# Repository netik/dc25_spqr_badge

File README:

In this folder you will find the KiCad board, schematic, and 
fabrication outputs for our Unofficial DEFCON 25 badge.

Stuff in the fabrication folder was set to MacroFab for prototype v1
on 12/20/2016. At today's prices, a board costs about $216 to make, or
$500 for two. This is for a 4-sided board and is not recommended.

Fabrication-rev4 contains our final and hopefully production gerbers.

Cost is approximately $180 / board for a single run, and this cost 
goes down as you make more boards.

The firmware is available in the cibios-orchard repo.
We are very close to release and this code is nearly in it's final 
form.
--
@netik
05/04/2017

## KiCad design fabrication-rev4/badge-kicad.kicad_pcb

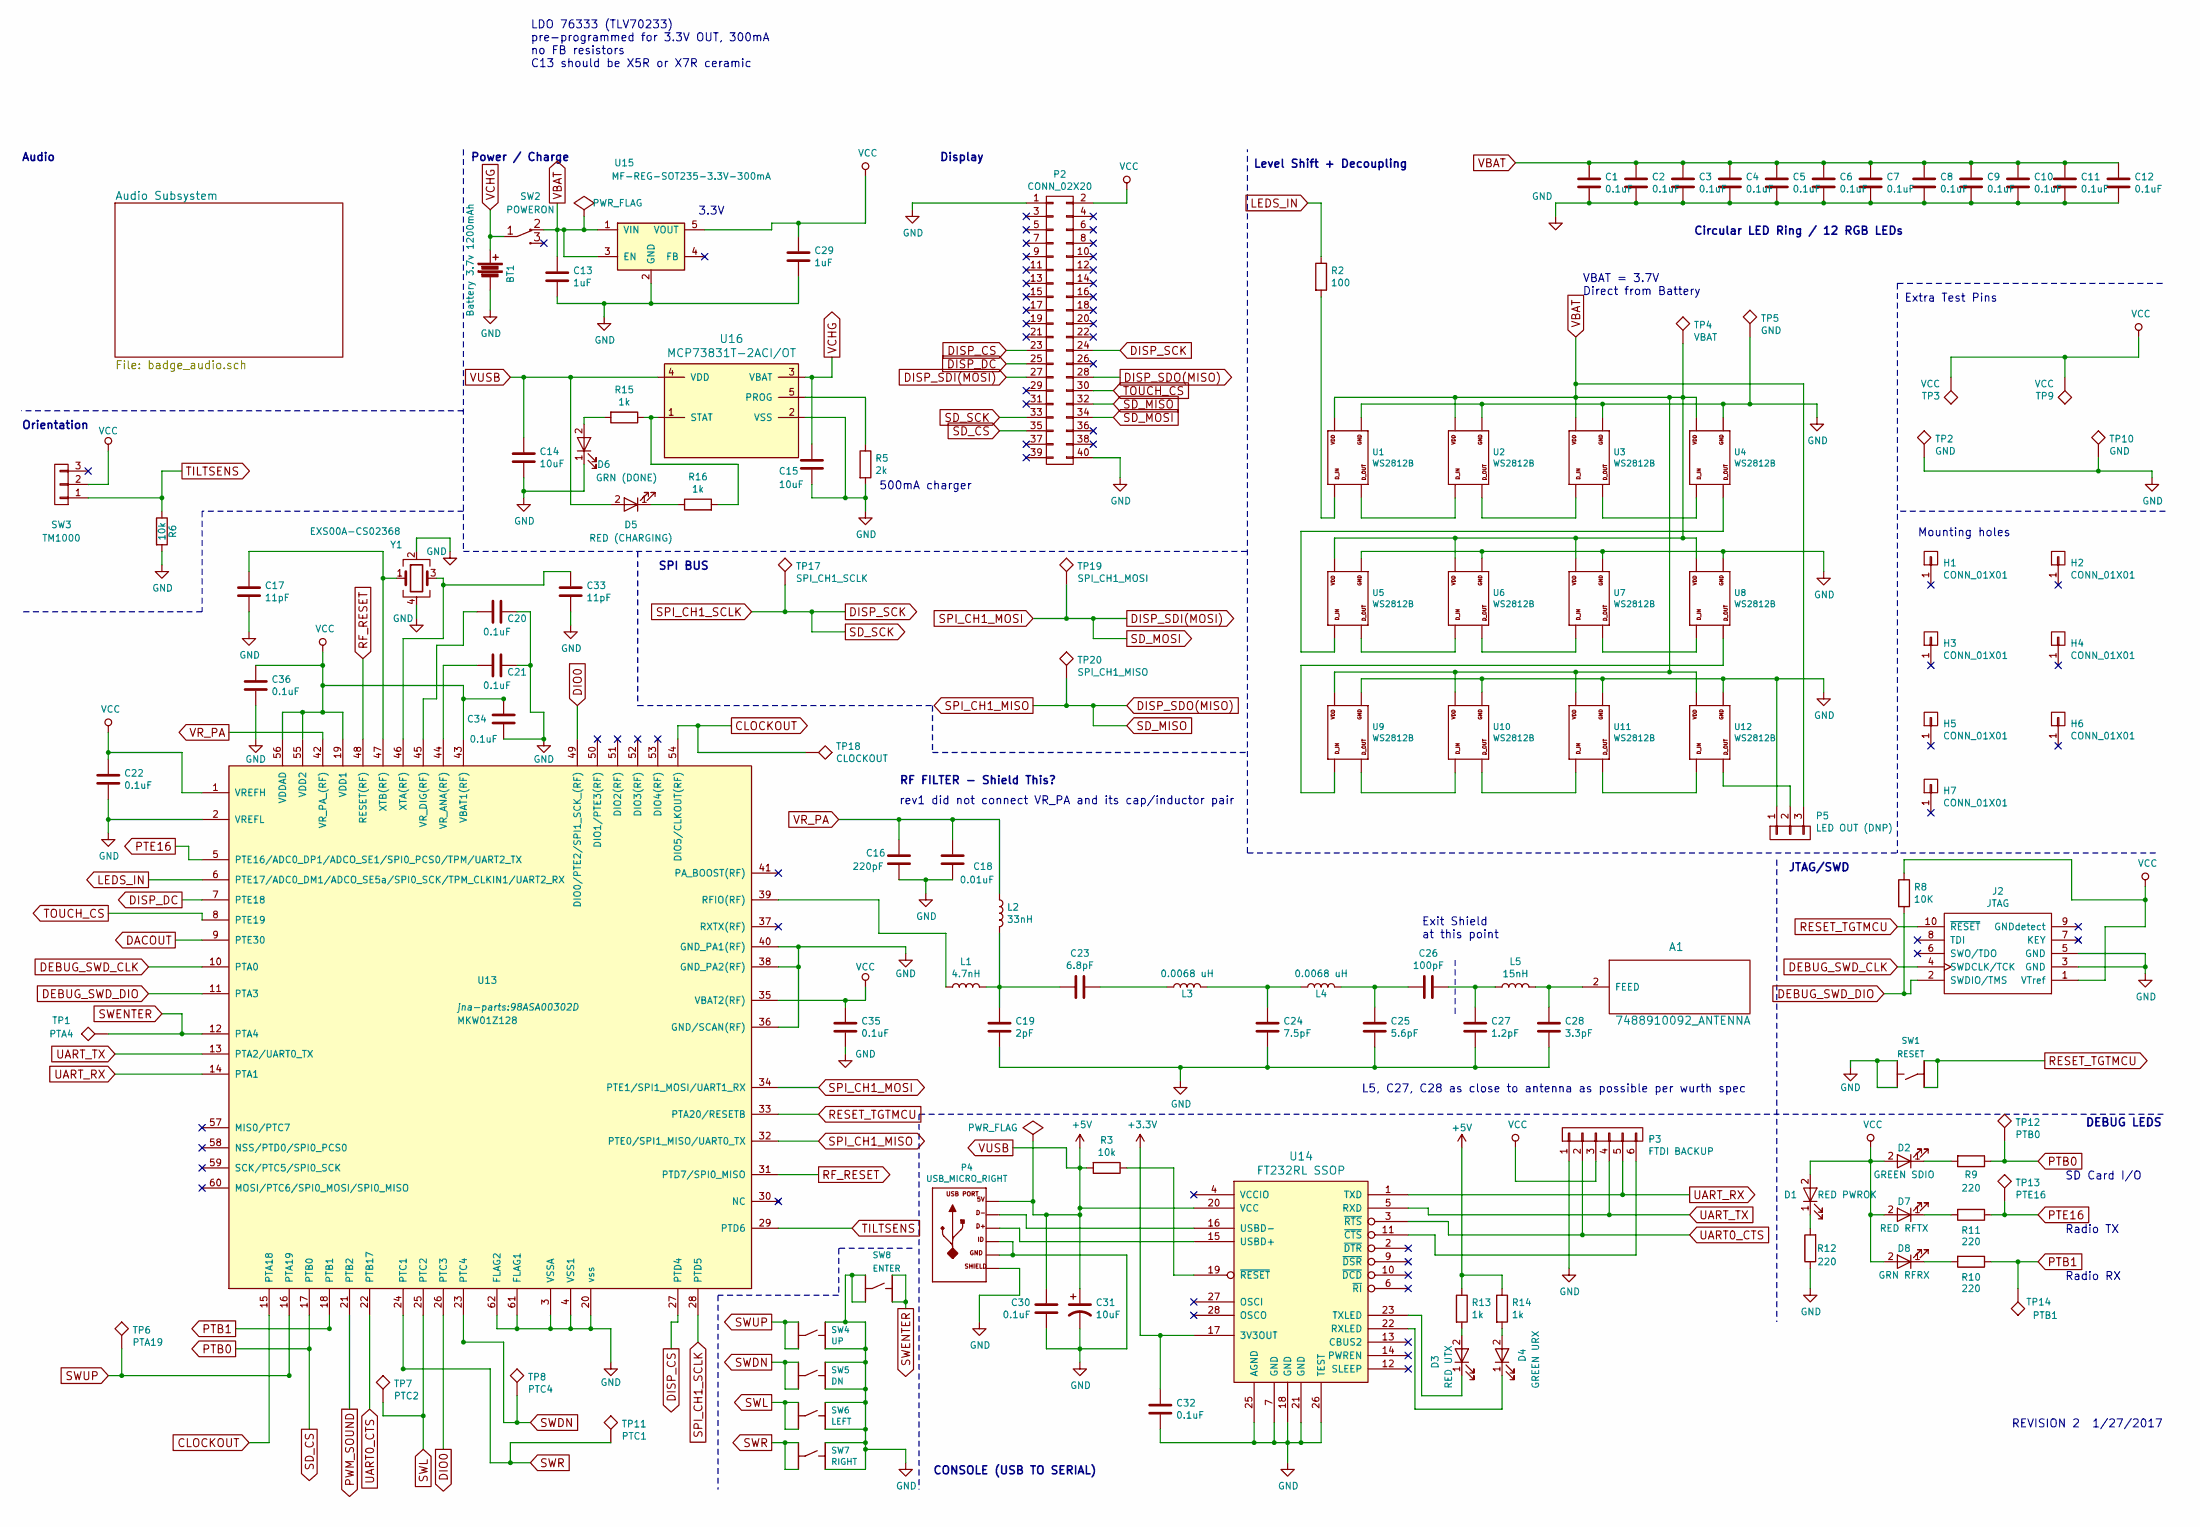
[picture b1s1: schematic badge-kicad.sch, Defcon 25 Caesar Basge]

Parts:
A1: 7488910092_ANTENNA; Antenna_Wurth_7488910092
BT1: Battery 3.7v 1200mAh; JST_PH_S2B-PH-SM4-TB_02x2.00mm_Angled
C1, C2, C3, C4, C5, C6, C7, C8, C9, C10, C11, C12, C20, C21, C22, C30, C32, C34, C35, C36: 0.1uF; C_0805_HandSoldering
C13, C29: 1uF; C_0805_HandSoldering
C14, C15: 10uF; C_1206
C16: 220pF; C_0805_HandSoldering
C17, C33: 11pF; C_0805_HandSoldering
C18: 0.01uF; C_0603_HandSoldering
C19: 2pF; C_0603_HandSoldering
C23: 6.8pF; C_0603_HandSoldering
C24: 7.5pF; C_0603_HandSoldering
C25: 5.6pF; C_0805_HandSoldering
C26: 100pF; C_0805_HandSoldering
C27: 1.2pF; C_0805_HandSoldering
C28: 3.3pF; C_0805_HandSoldering
C31: 10uF; C_0805_HandSoldering
D1: RED PWROK; LED_0805
D2: GREEN SDIO; LED_0805
D3: RED UTX; LED_0805
D4: GREEN URX; LED_0805
D5: RED (CHARGING); LED_0805
D6: GRN (DONE); LED_0805
D7: RED RFTX; LED_0805
D8: GRN RFRX; LED_0805
H1, H2, H3, H4, H5, H6, H7: CONN_01X01; MountingHole_3.2mm_M3_DIN965
J2: JTAG; Pin_Header_Straight_2x05_Pitch1.27mm
L1: 4.7nH; Neosid_Inductor_SM0603CG
L2: 33nH; Neosid_Inductor_SM0603CG
L3, L4: 0.0068 uH; Neosid_Inductor_SM0603CG
L5: 15nH; Neosid_Inductor_SM0603CG
P2: CONN_02X20; IDC_HEADER_FEMALE
P3: FTDI BACKUP; Pin_Header_Straight_1x06
P4: USB_MICRO_RIGHT; MF_Connectors-MICROUSB-RIGHT
P5: LED OUT (DNP); Pin_Header_Straight_1x03
R2: 100; R_0805
R3, R6: 10k; R_0805
R5: 2k; R_0805
R8: 10K; R_0805
R9, R10, R11, R12: 220; R_0805
R13, R14, R15, R16: 1k; R_0805
SW1: RESET; MF_Switches-TACT4.2MM
SW2: POWERON; SW_SPDT_PCM12
SW3: TM1000
SW4: UP; MF_Switches-TACT4.2MM
SW5: DN; MF_Switches-TACT4.2MM
SW6: LEFT; MF_Switches-TACT4.2MM
SW7: RIGHT; MF_Switches-TACT4.2MM
SW8: ENTER; MF_Switches-TACT4.2MM
TP1: PTA4; Measurement_Point_Round-TH_Small
TP2, TP5, TP10: GND; Measurement_Point_Round-TH_Small
TP3, TP9: VCC; Measurement_Point_Round-TH_Small
TP4: VBAT; Measurement_Point_Round-TH_Small
TP6: PTA19; Measurement_Point_Round-TH_Small
TP7: PTC2; Measurement_Point_Round-TH_Small
TP8: PTC4; Measurement_Point_Round-TH_Small
TP11: PTC1; Measurement_Point_Round-TH_Small
TP12: PTB0; Measurement_Point_Round-TH_Small
TP13: PTE16; Measurement_Point_Round-TH_Small
TP14: PTB1; Measurement_Point_Round-TH_Small
TP17: SPI_CH1_SCLK; Measurement_Point_Round-TH_Small
TP18: CLOCKOUT; Measurement_Point_Round-TH_Small
TP19: SPI_CH1_MOSI; Measurement_Point_Round-TH_Small
TP20: SPI_CH1_MISO; Measurement_Point_Round-TH_Small
U1, U2, U3, U4, U5, U6, U7, U8, U9, U10, U11, U12: WS2812B; MF_LEDs-WS2812B
U13: MKW01Z128; 98ASA00302D
U14: FT232RL SSOP; SSOP-28_5.3x10.2mm_Pitch0.65mm
U15: MF-REG-SOT235-3.3V-300mA; SOT-23-5
U16: MCP73831T-2ACI/OT; SOT-23-5
Y1: EXS00A-CS02368; Crystal_EXS00A-CS02368

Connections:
+3V3: C32.1, U14.17 (3V3OUT)
CLOCKOUT: TP18.1, U13.15 (PTA18), U13.54 (DIO5/CLKOUT(RF))
DACOUT: U13.9 (PTE30); also elsewhere on the board
DEBUG_SWD_CLK: J2.4 (SWDCLK/TCK), U13.10 (PTA0)
DEBUG_SWD_DIO: J2.2 (SWDIO/TMS), R8.2, U13.11 (PTA3)
DIO0: U13.26 (PTC3), U13.49 (DIO0/PTE2/SPI1_SCK_(RF))
DISP_CS: P2.23, U13.27 (PTD4)
DISP_DC: P2.25, U13.7 (PTE18)
DISP_SCK: P2.24, P2.33, TP17.1, U13.28 (PTD5)
DISP_SDI(MOSI): P2.27, P2.34, TP19.1, U13.34 (PTE1/SPI1_MOSI/UART1_RX)
DISP_SDO(MISO): P2.28, P2.32, TP20.1, U13.32 (PTE0/SPI1_MISO/UART0_TX)
GND: BT1.2, C1.2, C2.2, C3.2, C4.2, C5.2, C6.2, C7.2, C8.2, C9.2, C10.2, C11.2, C12.2, C13.2, C14.2, C15.2, C16.2, C17.2, C18.2, C19.2, C20.1, C21.1, C22.2, C24.2, C25.2, C27.2, C28.2, C29.2, C30.2, C31.2, C32.2, C33.2, C34.1, C35.2, C36.2, D6.1 (K), J2.3 (GND), J2.5 (GND), P2.1, P2.40, P3.1, P4.4 (ID), P4.5 (GND), P4.S1 (SLD), P4.S2 (SLD), P4.S3 (SLD), P4.S4 (SLD), P4.S5 (SLD), P4.S6 (SLD), P5.1, R5.2, R6.2, R12.1, SW1.P$1, SW1.P$2, SW4.P$1, SW4.P$2, SW5.P$1, SW5.P$2, SW6.P$1, SW6.P$2, SW7.P$1, SW7.P$2, SW8.P$3, SW8.P$4, TP2.1, TP5.1, TP10.1, U1.P$3 (VSS), U2.P$3 (VSS), U3.P$3 (VSS), U4.P$3 (VSS), U5.P$3 (VSS), U6.P$3 (VSS), U7.P$3 (VSS), U8.P$3 (VSS), U9.P$3 (VSS), U10.P$3 (VSS), U11.P$3 (VSS), U12.P$3 (VSS), U13.2 (VREFL), U13.3 (VSSA), U13.4 (VSS1), U13.20 (vss), U13.36 (GND/SCAN(RF)), U13.38 (GND_PA2(RF)), U13.40 (GND_PA1(RF)), U13.61 (FLAG1), U13.62 (FLAG2), U14.7 (GND), U14.18 (GND), U14.21 (GND), U14.25 (AGND), U14.26 (TEST), U15.2 (GND), U16.2 (VSS), Y1.2, Y1.4; also elsewhere on the board
LEDS_IN: R2.1, U13.6 (PTE17/ADC0_DM1/ADCO_SE5a/SPI0_SCK/TPM_C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)
unnamed: A1.2 (FEED), C28.1, L5.2
unnamed: C17.1, U13.47 (XTB(RF)), Y1.1
unnamed: C19.1, C23.2, L1.2, L2.2
unnamed: C20.2, U13.45 (VR_DIG(RF))
unnamed: C21.2, U13.44 (VR_ANA(RF))
unnamed: C23.1, L3.1
unnamed: C24.1, L3.2, L4.1
unnamed: C25.1, C26.2, L4.2
unnamed: C26.1, C27.1, L5.1
unnamed: C33.1, U13.46 (XTA(RF)), Y1.3
unnamed: D1.1 (K), R12.2
unnamed: D2.1 (K), R9.2
unnamed: D3.1 (K), U14.23 (TXLED)
unnamed: D3.2 (A), R13.2
unnamed: D4.1 (K), U14.22 (RXLED)
unnamed: D4.2 (A), R14.2
unnamed: D5.1 (K), R16.1
unnamed: D6.2 (A), R15.2
unnamed: D7.1 (K), R11.2
unnamed: D8.1 (K), R10.2
unnamed: L1.1, U13.39 (RFIO(RF))
unnamed: P3.6, U14.11 (~CTS)
unnamed: P4.2 (D-), U14.16 (USBD-)
unnamed: P4.3 (D+), U14.15 (USBD+)
unnamed: P5.2, U12.P$2 (DOUT)
unnamed: R2.2, U1.P$4 (DIN)
unnamed: R3.1, U14.19 (~RESET)
unnamed: R5.1, U16.5 (PROG)
unnamed: R15.1, R16.2, U16.1 (STAT)
unnamed: U1.P$2 (DOUT), U2.P$4 (DIN)
unnamed: U2.P$2 (DOUT), U3.P$4 (DIN)
unnamed: U3.P$2 (DOUT), U4.P$4 (DIN)
unnamed: U4.P$2 (DOUT), U5.P$4 (DIN)
unnamed: U5.P$2 (DOUT), U6.P$4 (DIN)
unnamed: U6.P$2 (DOUT), U7.P$4 (DIN)
unnamed: U7.P$2 (DOUT), U8.P$4 (DIN)
unnamed: U8.P$2 (DOUT), U9.P$4 (DIN)
unnamed: U10.P$2 (DOUT), U11.P$4 (DIN)
unnamed: U9.P$2 (DOUT), U10.P$4 (DIN)
unnamed: U11.P$2 (DOUT), U12.P$4 (DIN)
PTB0: P2.35, R9.1, TP12.1, U13.17 (PTB0)
PTB1: R10.1, TP14.1, U13.18 (PTB1)
PTE16: R11.1, TP13.1, U13.5 (PTE16/ADC0_DP1/ADCO_SE1/SPI0_PCS0/TPM/U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)
PWM_SOUND: U13.21 (PTB2); also elsewhere on the board
RESET_TGTMCU: J2.10 (~RESET), SW1.P$3, SW1.P$4, U13.33 (PTA20/RESETB)
RF_RESET: U13.31 (PTD7/SPI0_MISO), U13.48 (RESET(RF))
SWDN: SW5.P$3, SW5.P$4, TP8.1, U13.23 (PTC4)
SWENTER: SW8.P$1, SW8.P$2, TP1.1, U13.12 (PTA4)
SWL: SW6.P$3, SW6.P$4, TP7.1, U13.25 (PTC2)
SWR: SW7.P$3, SW7.P$4, TP11.1, U13.24 (PTC1)
SWUP: SW4.P$3, SW4.P$4, TP6.1, U13.16 (PTA19)
TILTSENS: R6.1, SW3.1, U13.29 (PTD6)
TOUCH_CS: P2.30, U13.8 (PTE19)
UART0_CTS: P3.2, U13.22 (PTB17), U14.3 (~RTS)
UART_RX: P3.5, U13.14 (PTA1), U14.1 (TXD)
UART_TX: P3.4, U13.13 (PTA2/UART0_TX), U14.5 (RXD)
VBAT: C1.1, C2.1, C3.1, C4.1, C5.1, C6.1, C7.1, C8.1, C9.1, C10.1, C11.1, C12.1, C13.1, P5.3, SW2.2 (NC), TP4.1, U1.P$1 (VDD), U2.P$1 (VDD), U3.P$1 (VDD), U4.P$1 (VDD), U5.P$1 (VDD), U6.P$1 (VDD), U7.P$1 (VDD), U8.P$1 (VDD), U9.P$1 (VDD), U10.P$1 (VDD), U11.P$1 (VDD), U12.P$1 (VDD), U15.1 (VIN), U15.3 (EN); also elsewhere on the board
VCC: C22.1, C29.1, C34.2, C35.1, C36.1, D1.2 (A), D2.2 (A), D7.2 (A), D8.2 (A), J2.1 (VTref), P2.2, P3.3, R8.1, SW3.2, TP3.1, TP9.1, U13.1 (VREFH), U13.19 (VDD1), U13.35 (VBAT2(RF)), U13.43 (VBAT1(RF)), U13.55 (VDD2), U13.56 (VDDAD), U15.5 (VOUT)
VCHG: BT1.1, C15.1, SW2.1 (COM), U16.3 (VBAT)
VR_PA: C16.1, C18.1, L2.1, U13.42 (VR_PA_(RF))
VUSB: C14.1, C30.1, C31.1, D5.2 (A), P4.1 (5V), R3.2, R13.1, R14.1, U14.20 (VCC), U16.4 (VDD)

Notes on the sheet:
Level Shift + Decoupling
Circular LED Ring / 12 RGB LEDs
JTAG/SWD
Display
Audio
Power / Charge
RF FILTER - Shield This?
SPI BUS
Orientation
CONSOLE (USB TO SERIAL)
DEBUG LEDS
LDO 76333 (TLV70233) pre-programmed for 3.3V OUT, 300mA no FB resistors C13 should be X5R or X7R ceramic
500mA charger
3.3V
VBAT = 3.7V Direct from Battery
Radio RX
Radio TX
SD Card I/O
rev1 did not connect VR_PA and its cap/inductor pair
L5, C27, C28 as close to antenna as possible per wurth spec
Exit Shield at this point
Mounting holes
Extra Test Pins
REVISION 2 1/27/2017

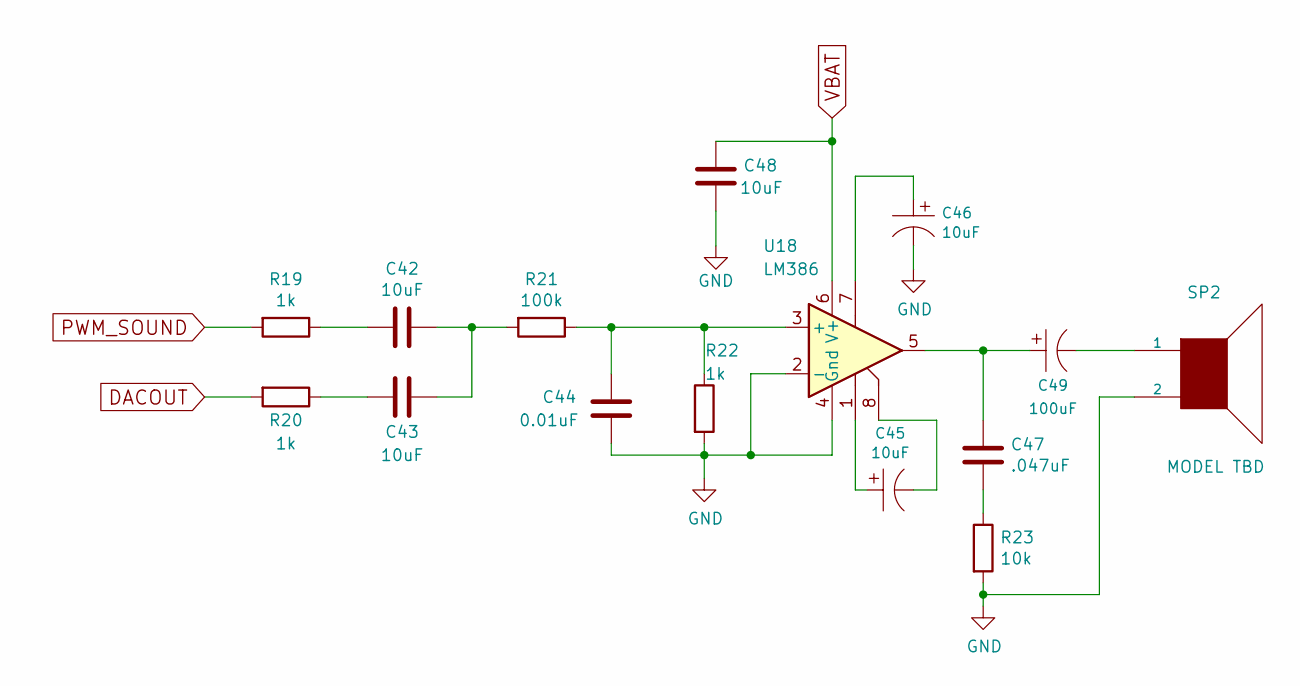
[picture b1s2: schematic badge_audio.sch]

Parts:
C42, C43, C48: 10uF; C_0805_HandSoldering
C44: 0.01uF; C_0603_HandSoldering
C45, C46: 10uF; MF_Passives-CP4MM
C47: .047uF; C_0805_HandSoldering
C49: 100uF; MF_Passives-CP6.3MM
R19, R20, R22: 1k; R_0805
R21: 100k; R_0805
R23: 10k; R_0805
SP2: MODEL TBD; SPEAKER_AST_01708MR_R
U18: LM386; SOIC-8-N

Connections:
DACOUT: R20.2; also elsewhere on the board
GND: C44.2, C46.P$2, C48.2, R22.2, R23.2, SP2.2, U18.2 (-), U18.4 (Gnd); also elsewhere on the board
unnamed: C42.1, C43.1, R21.2
unnamed: C42.2, R19.1
unnamed: C43.2, R20.1
unnamed: C44.1, R21.1, R22.1, U18.3 (+)
unnamed: C45.P$1, U18.1
unnamed: C45.P$2, U18.8
unnamed: C46.P$1, U18.7
unnamed: C47.1, C49.P$1, U18.5
unnamed: C47.2, R23.1
unnamed: C49.P$2, SP2.1
PWM_SOUND: R19.2; also elsewhere on the board
VBAT: C48.1, U18.6 (V+); also elsewhere on the board

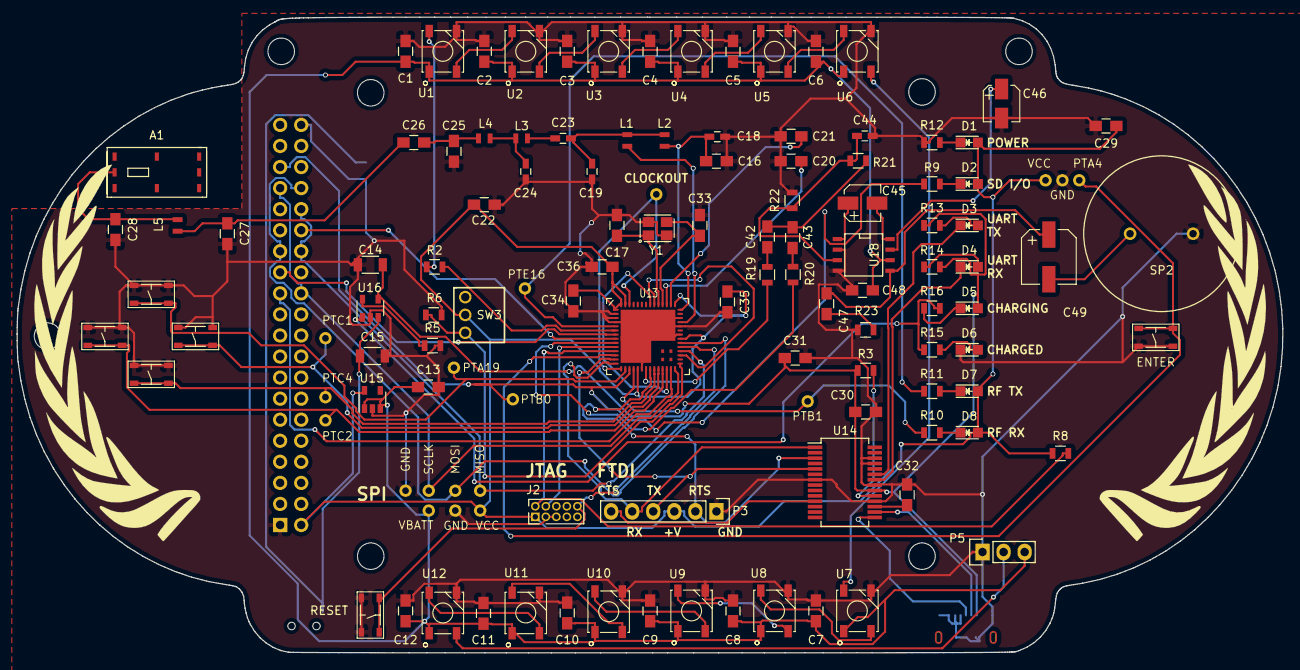
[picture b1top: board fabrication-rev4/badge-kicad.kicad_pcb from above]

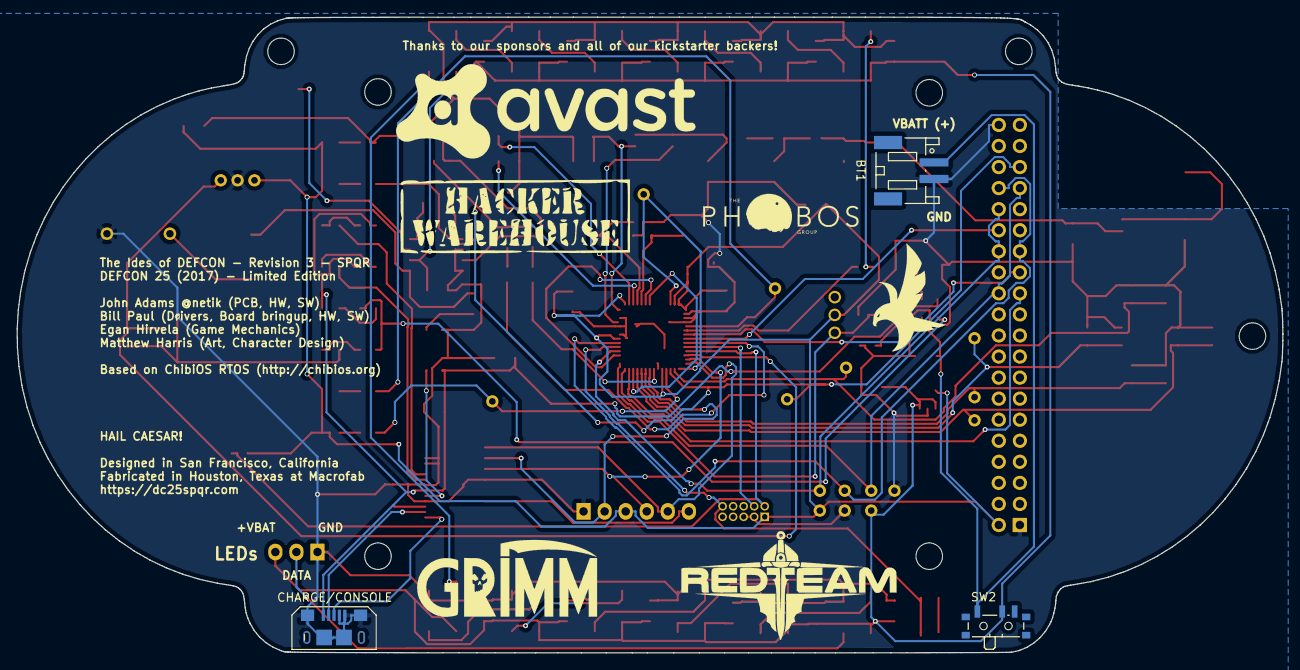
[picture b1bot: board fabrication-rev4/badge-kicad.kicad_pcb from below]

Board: 2 copper layers, 152.7 x 76.7 mm, 134 parts (3 on the bottom side), 84 nets.

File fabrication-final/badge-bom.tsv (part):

# Generated by MacroFab for PCB 4dj0a6, version 10.
# DESIGNATOR	X_LOC	Y_LOC	ROTATION	SIDE	TYPE	X_SIZE	Y_SIZE	VALUE	FOOTPRINT	POPULATE	MPN	MPN1	MPN2	MPN3
""	2381.84	2081.92	180	2	2	0	0	"	logos:phobos_19mm_x_5.5mm	0					
""	2381.84	2081.92	180	2	2	0	0	"	logos:hw_200dpi	0					
""	2381.84	2081.92	180	2	2	0	0	"	logos:grimm_600dpi	0					
""	2381.84	2081.92	180	2	2	0	0	"	logos:redteam_31_40	0					
""	2381.84	2081.92	180	2	2	0	0	"	logos:laurel_right	0					
""	2381.84	2081.92	180	2	2	0	0	"	logos:laurel	0					
A1	663.338	2281.92	180	1	1	421.26	188.976	7488910092_ANTENNA	jna-parts:Antenna_Wurth_7488910092	1	7488910092				7488910092
BT1	1764.72	2289.79	270	2	1	330.709	354.331	Battery 3.7v 1000mAh	Connectors_JST:JST_PH_S2B-PH-SM4-TB_02x2.00mm_Angled	1	1769				1769
C1	1844.44	2856.72	90	1	1	157.48	49.2126	0.1uF	Capacitors_SMD:C_0805_HandSoldering	1					
C10	2612.16	189.4	90	1	1	157.48	49.2126	0.1uF	Capacitors_SMD:C_0805_HandSoldering	1					
C11	2214.52	187.431	90	1	1	157.48	49.2126	0.1uF	Capacitors_SMD:C_0805_HandSoldering	1					
C12	1844.44	199.242	90	1	1	157.48	49.2126	0.1uF	Capacitors_SMD:C_0805_HandSoldering	1					
C13	1952.71	1262.23	0	1	1	157.48	49.2126	1uF	Capacitors_SMD:C_0805_HandSoldering	1					
C14	1677.12	1842.94	180	1	1	157.48	62.9921	10uF	Capacitors_SMD:C_1206	1					
C15	1686.96	1409.87	0	1	1	157.48	62.9921	10uF	Capacitors_SMD:C_1206	1					
C16	3320.82	2335.07	0	1	1	157.48	49.2126	220pF	Capacitors_SMD:C_0805_HandSoldering	1	C0805C221K5GACTU				C0805C221K5GACTU
C17	2848.38	2029.95	90	1	1	157.48	49.2126	11pF	Capacitors_SMD:C_0805_HandSoldering	1	C0805C110J5GACTU				C0805C110J5GACTU
C18	3324.75	2451.21	0	1	1	122.047	29.5276	0.01uF	Capacitors_SMD_C_0603_HandSoldering	1	MF-CAP-0603-0.01uF				MF-CAP-0603-0.01uF
C19	2730.27	2285.86	270	1	1	122.047	29.5276	2pF	Capacitors_SMD:C_0603_HandSoldering	1	C1608C0G1H020C080AA				C1608C0G1H020C080AA
C2	2218.46	2856.72	90	1	1	157.48	49.2126	0.1uF	Capacitors_SMD:C_0805_HandSoldering	1					
C20	3675.15	2335.07	0	1	1	157.48	49.2126	0.1uF	Capacitors_SMD:C_0805_HandSoldering	1					
C21	3675.15	2453.18	0	1	1	157.48	49.2126	0.1uF	Capacitors_SMD:C_0805_HandSoldering	1					
C22	2218.46	2128.38	0	1	1	157.48	49.2126	0.1uF	Capacitors_SMD:C_0805_HandSoldering	1					
C23	2592.47	2443.34	0	1	1	122.047	29.5276	6.8pF	Capacitors_SMD_C_0603_HandSoldering	1	06035A6R8CAT2A				06035A6R8CAT2A
C24	2415.31	2285.86	270	1	1	122.047	29.5276	7.5pF	0603	1	251R14S7R5CV4T				251R14S7R5CV4T
C25	2074.36	2381.92	270	1	1	157.48	49.2126	5.6pF	Capacitors_SMD:C_0805_HandSoldering	1	CL21C5R6CBANNNC				CL21C5R6CBANNNC
C26	1883.81	2423.65	0	1	1	157.48	49.2126	100pF	Capacitors_SMD:C_0805_HandSoldering	1	08055A101KAT2A				08055A101KAT2A
C27	997.983	1990.58	270	1	1	157.48	49.2126	1.2pF	Capacitors_SMD:C_0805_HandSoldering	1	CL21C1R2BBANNNC				CL21C1R2BBANNNC
C28	466.487	2010.27	270	1	1	157.48	49.2126	3.3pF	Capacitors_SMD:C_0805_HandSoldering	1	08055A3R3CAT2A				08055A3R3CAT2A
C29	5171.21	2502.39	180	1	1	157.48	49.2126	1uF	Capacitors_SMD:C_0805_HandSoldering	1					
C3	2612.16	2856.72	90	1	1	157.48	49.2126	0.1uF	Capacitors_SMD:C_0805_HandSoldering	1					
C30	4029.48	1144.12	0	1	1	157.48	49.2126	0.1uF	Capacitors_SMD:C_0805_HandSoldering	1					
C31	3694.83	1400.03	0	1	1	157.48	49.2126	10uF	Capacitors_SMD:C_0805_HandSoldering	1	CL21A106KQCLRNC				CL21A106KQCLRNC
C32	4226.33	750.423	90	1	1	157.48	49.2126	0.1uF	Capacitors_SMD:C_0805_HandSoldering	1					
C33	3242.08	2029.95	90	1	1	157.48	49.2126	11pF	Capacitors_SMD:C_0805_HandSoldering	1	C0805C110J5GACTU				C0805C110J5GACTU
C34	2641.29	1671.29	90	1	1	157.48	49.2126	0.1uF	Capacitors_SMD:C_0805_HandSoldering	1					
C35	3372.98	1666.76	270	1	1	157.48	49.2126	0.1uF	Capacitors_SMD:C_0805_HandSoldering	1					
C36	2777.9	1833.1	180	1	1	157.48	49.2126	0.1uF	Capacitors_SMD:C_0805_HandSoldering	1					
C4	3005.86	2856.72	90	1	1	157.48	49.2126	0.1uF	Capacitors_SMD:C_0805_HandSoldering	1					
C42	3562.55	1975.23	270	1	1	157.48	49.2126	10uF	Capacitors_SMD:C_0805_HandSoldering	1	CL21A106KQCLRNC				CL21A106KQCLRNC
C43	3682.63	1971.68	270	1	1	157.48	49.2126	Capacitors_SMD:C_0805_HandSoldering	1	1	CL21A106KQCLRNC			CL21A106KQCLRNC	CL21A106KQCLRNC
C44	4025.54	2455.15	0	1	1	122.047	29.5276	0.01uF	Capacitors_SMD_C_0603_HandSoldering	1	MF-CAP-0603-0.01uF				MF-CAP-0603-0.01uF
C45	4014.52	2135.86	270	1	1	98.4	200.5	10uF	MF_Passives:MF_Passives-CP4MM	1	MF-CAP-4MM-10uF				MF-CAP-4MM-10uF
C46	4675.15	2608.69	180	1	1	98.4	200.5	10uF	MF_Passives:MF_Passives-CP4MM	1	MF-CAP-4MM-10uF				MF-CAP-4MM-10uF
C47	3844.05	1657.9	270	1	1	157.48	49.2126	.047uF	Capacitors_SMD:C_0805_HandSoldering	1	08053C473JAT2A				08053C473JAT2A
C48	4014.52	1721.68	180	1	1	157.48	49.2126	10uF	Capacitors_SMD:C_0805_HandSoldering	1	CL21A106KQCLRNC				CL21A106KQCLRNC
C49	4899.56	1880.34	180	1	1	125.9	275.3	100uF	MF_Passives:MF_Passives-CP6.3MM	1	MF-CAP-6.3MM-100uF				MF-CAP-6.3MM-100uF
C5	3399.56	2856.72	90	1	1	157.48	49.2126	0.1uF	Capacitors_SMD:C_0805_HandSoldering	1					
C6	3793.26	2856.72	90	1	1	157.48	49.2126	0.1uF	Capacitors_SMD:C_0805_HandSoldering	1					
C7	3793.26	199.242	90	1	1	157.48	49.2126	0.1uF	Capacitors_SMD:C_0805_HandSoldering	1					
C8	3399.56	199.242	90	1	1	157.48	49.2126	0.1uF	Capacitors_SMD:C_0805_HandSoldering	1					
C9	3005.86	199.242	90	1	1	157.48	49.2126	0.1uF	Capacitors_SMD:C_0805_HandSoldering	1					
D1	4521.61	2423.65	0	1	1	129.8	47.2	RED PWROK	LEDs:LED_0805	1	MF-LED-0805-RED				MF-LED-0805-RED
D2	4521.61	2226.8	0	1	1	129.8	47.2	GREEN SDIO	LEDs:LED_0805	1	MF-LED-0805-GREEN				MF-LED-0805-GREEN
D3	4521.61	2029.95	0	1	1	129.8	47.2	RED UTX	LEDs:LED_0805	1	MF-LED-0805-RED				MF-LED-0805-RED
D4	4521.61	1833.1	0	1	1	129.8	47.2	GREEN URX	LEDs:LED_0805	1	MF-LED-0805-GREEN				MF-LED-0805-GREEN
D5	4521.61	1636.25	0	1	1	129.8	47.2	RED (CHARGING)	LEDs:LED_0805	1	MF-LED-0805-RED				MF-LED-0805-RED
D6	4521.61	1439.4	0	1	1	129.8	47.2	GRN (DONE)	LEDs:LED_0805	1	MF-LED-0805-GREEN				MF-LED-0805-GREEN
D7	4521.61	1242.55	0	1	1	129.8	47.2	RED RFTX	LEDs:LED_0805	1	MF-LED-0805-RED				MF-LED-0805-RED
D8	4521.61	1045.7	0	1	1	129.8	47.2	GRN RFRX	LEDs:LED_0805	1	MF-LED-0805-GREEN				MF-LED-0805-GREEN
H1	1679.09	2659.87	0	1	2	125.984	125.984	CONN_01X01	Mounting_Holes_MountingHole_3_2mm_M3_DIN965	0					
H2	4297.2	2663.81	0	1	2	125.984	125.984	CONN_01X01	Mounting_Holes_MountingHole_3_2mm_M3_DIN965	0					
H3	1679.09	459.085	0	1	2	125.984	125.984	CONN_01X01	Mounting_Holes_MountingHole_3_2mm_M3_DIN965	0					
H4	4297.2	459.085	0	1	2	125.984	125.984	CONN_01X01	Mounting_Holes_MountingHole_3_2mm_M3_DIN965	0					
H5	1253.89	2856.72	0	1	2	125.984	125.984	CONN_01X01	Mounting_Holes_MountingHole_3_2mm_M3_DIN965	0					
H6	4757.83	2856.72	0	1	2	125.984	125.984	CONN_01X01	Mounting_Holes_MountingHole_3_2mm_M3_DIN965	0					
H7	144.046	1504.2	0	1	2	125.984	125.984	CONN_01X01	Mounting_Holes_MountingHole_3_2mm_M3_DIN965	0					
J2	2560.58	671.093	90	1	2	91.3386	241.339	JTAG	Pin_Headers:Pin_Header_Straight_2x05_Pitch1.27mm	1	M50-3500542				M50-3500542
L1	2897.59	2433.49	90	1	1	78.8	47.2	4.7nH	Inductors_NEOSID:Neosid_Inductor_SM0603CG	1	LQG18HN4N7S00D				LQG18HN4N7S00D
L2	3074.75	2433.49	90	1	1	78.8	47.2	33nH	Inductors_NEOSID:Neosid_Inductor_SM0603CG	1	CI160808-33NJ				CI160808-33NJ
L3	2395.62	2443.34	180	1	1	78.8	47.2	0.0068 uH	Inductors_NEOSID:Neosid_Inductor_SM0603CG	1	CI160808-6N8J				CI160808-6N8J
L4	2218.46	2443.34	180	1	1	78.8	47.2	0.0068 uH	Inductors_NEOSID:Neosid_Inductor_SM0603CG	1	CI160808-6N8J				CI160808-6N8J
L5	761.763	2029.95	90	1	1	78.8	47.2	15nH	Inductors_NEOSID_Neosid_Inductor_SM0603CG	1	HK160815NJ-T				HK160815NJ-T
P2	1298.77	1557.19	90	1	2	1968	168	CONN_02X20	jna-parts:IDC_HEADER_FEMALE	1	SFH11-PBPC-D20-ST-BK				SFH11-PBPC-D20-ST-BK
P3	3070.82	671.683	270	1	2	80	568	FTDI BACKUP	Pin_Headers_Pin_Header_Straight_1x06	0					
P4	4505.86	122.751	180	2	1	306.9	174.15	USB_MICRO_RIGHT	MF_Connectors:MF_Connectors-MICROUSB-RIGHT	1	105017-0001				MF-CON-MICROUSB-RIGHT
P5	4684.6	478.77	90	1	2	80	268	LED OUT (DNP)	Pin_Headers_Pin_Header_Straight_1x03	0					
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
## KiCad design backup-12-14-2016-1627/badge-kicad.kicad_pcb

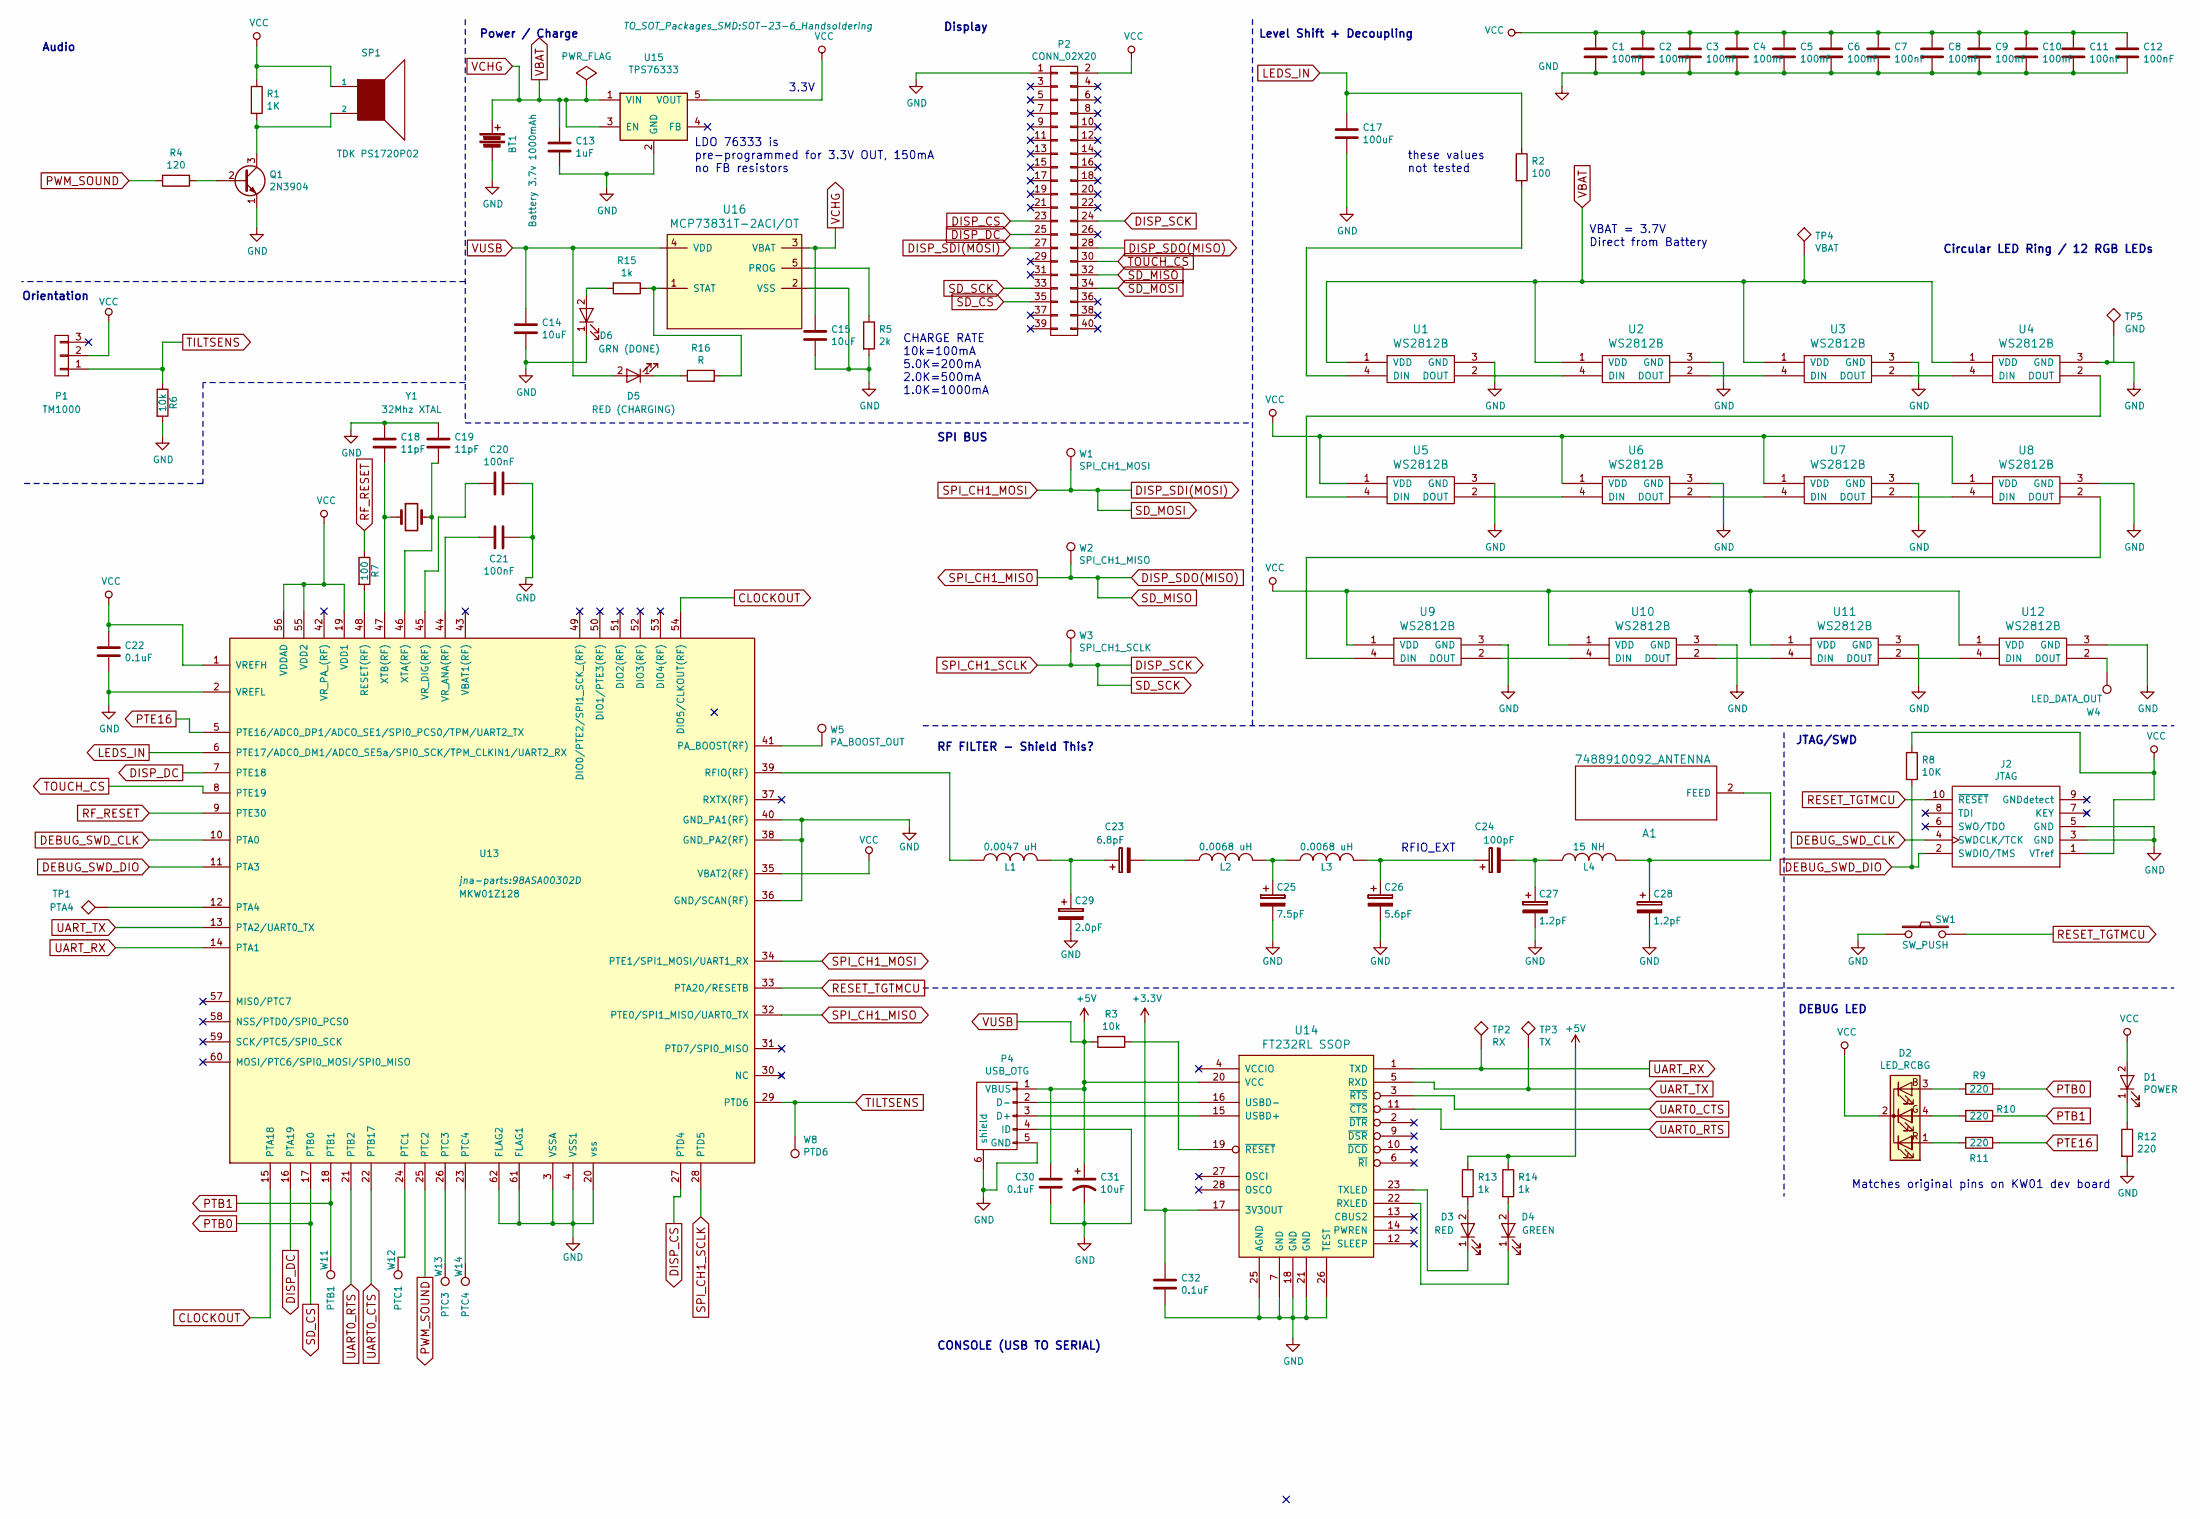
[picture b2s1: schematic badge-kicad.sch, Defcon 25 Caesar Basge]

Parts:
A1: 7488910092_ANTENNA; Antenna_Wurth_7488910092
BT1: Battery 3.7v 1000mAh; JST_PH_S2B-PH-SM4-TB_02x2.00mm_Angled
C1, C2, C3, C4, C5, C6, C7, C8, C9, C10, C11, C12, C20, C21: 100nF; C_1206
C13: 1uF; C_1206
C14, C15, C31: 10uF; C_1206
C17: 100uF; C_1206
C18, C19: 11pF; C_1206
C22, C30, C32: 0.1uF; C_1206
C23: 6.8pF; C_1206
C24: 100pF; C_1206
C25: 7.5pF; C_1206
C26: 5.6pF; C_1206
C27, C28: 1.2pF; C_1206
C29: 2.0pF; C_1206
D1: POWER; LED_1206
D2: LED_RCBG; LED-RGB-5MM_Common_Cathode
D3: RED; LED_1206
D4: GREEN; LED_1206
D5: RED (CHARGING); LED_1206
D6: GRN (DONE); LED_1206
J2: JTAG; IDC_Header_Straight_10pins
L1: 0.0047 uH; Neosid_Inductor_SM1206
L2, L3: 0.0068 uH; Neosid_Inductor_SM1206
L4: 15 NH; Neosid_Inductor_SM1206
P1: TM1000
P2: CONN_02X20; IDC_Header_Straight_40pins
P4: USB_OTG; USB_Mini-B
Q1: 2N3904; SOT-323
R1: 1K; R_1206
R2, R7: 100; R_1206
R3, R6: 10k; R_1206
R4: 120; R_1206
R5: 2k; R_1206
R8: 10K; R_1206
R9, R10, R11, R12: 220; R_1206
R13, R14, R15: 1k; R_1206
R16: R; R_1206
SP1: TDK PS1720P02; TDK_PS1720PD2
SW1: SW_PUSH; SW_SPST_B3S-1000
TP1: PTA4; Test_Point_Keystone_5005-5009_Compact
TP2: RX; Test_Point_Keystone_5005-5009_Compact
TP3: TX; Test_Point_Keystone_5005-5009_Compact
TP4: VBAT; Test_Point_Keystone_5005-5009_Compact
TP5: GND; Test_Point_Keystone_5005-5009_Compact
U1, U2, U3, U4, U5, U6, U7, U8, U9, U10, U11, U12: WS2812B; LED_WS2812B-PLCC4
U13: MKW01Z128; 98ASA00302D
U14: FT232RL SSOP; SSOP-28_5.3x10.2mm_Pitch0.65mm
U15: TPS76333; SOT-23-6_Handsoldering
U16: MCP73831T-2ACI/OT; SOT-23-5
W1: SPI_CH1_MOSI; Test_Point_Keystone_5005-5009_Compact
W2: SPI_CH1_MISO; Test_Point_Keystone_5005-5009_Compact
W3: SPI_CH1_SCLK; Test_Point_Keystone_5005-5009_Compact
W4: LED_DATA_OUT; Test_Point_Keystone_5005-5009_Compact
W5: PA_BOOST_OUT; Test_Point_Keystone_5005-5009_Compact
W8: PTD6; Test_Point_Keystone_5005-5009_Compact
W11: PTB1; Test_Point_Keystone_5005-5009_Compact
W12: PTC1; Test_Point_Keystone_5005-5009_Compact
W13: PTC3; Test_Point_Keystone_5005-5009_Compact
W14: PTC4; Test_Point_Keystone_5005-5009_Compact
Y1: 32Mhz XTAL; Crystal_SMD_0603_4Pads

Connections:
+3V3: C32.1, U14.17 (3V3OUT)
CLOCKOUT: U13.15 (PTA18), U13.54 (DIO5/CLKOUT(RF))
DEBUG_SWD_CLK: J2.4 (SWDCLK/TCK), U13.10 (PTA0)
DEBUG_SWD_DIO: J2.2 (SWDIO/TMS), R8.2, U13.11 (PTA3)
DISP_CS: P2.23, U13.27 (PTD4)
DISP_DC: P2.25, U13.7 (PTE18), U13.16 (PTA19)
DISP_SCK: P2.24, P2.33, U13.28 (PTD5), W3.1
DISP_SDI(MOSI): P2.27, P2.34, U13.34 (PTE1/SPI1_MOSI/UART1_RX), W1.1
DISP_SDO(MISO): P2.28, P2.32, U13.32 (PTE0/SPI1_MISO/UART0_TX), W2.1
GND: BT1.2, C1.2, C2.2, C3.2, C4.2, C5.2, C6.2, C7.2, C8.2, C9.2, C10.2, C11.2, C12.2, C13.2, C14.2, C15.2, C17.2, C18.1, C19.1, C20.1, C21.1, C22.2, C25.2, C26.2, C27.2, C28.2, C29.2, C30.2, C31.2, C32.2, D6.1 (K), J2.3 (GND), J2.5 (GND), P2.1, P4.4 (ID), P4.5 (GND), P4.6 (shield), Q1.1 (E), R5.2, R6.2, R12.2, SW1.1, TP5.1, U1.3 (GND), U2.3 (GND), U3.3 (GND), U4.3 (GND), U5.3 (GND), U6.3 (GND), U7.3 (GND), U8.3 (GND), U9.3 (GND), U10.3 (GND), U11.3 (GND), U12.3 (GND), U13.2 (VREFL), U13.3 (VSSA), U13.4 (VSS1), U13.20 (vss), U13.36 (GND/SCAN(RF)), U13.38 (GND_PA2(RF)), U13.40 (GND_PA1(RF)), U13.61 (FLAG1), U13.62 (FLAG2), U14.7 (GND), U14.18 (GND), U14.21 (GND), U14.25 (AGND), U14.26 (TEST), U15.2 (GND), U16.2 (VSS)
LEDS_IN: C17.1, R2.1, U13.6 (PTE17/ADC0_DM1/ADCO_SE5a/SPI0_SCK/TPM_C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)
unnamed 11: R3.1, U14.19 (~RESET); also elsewhere on the board
unnamed: A1.2 (FEED), C28.1, L4.2
unnamed: C18.2, U13.47 (XTB(RF)), Y1.1
unnamed: C19.2, U13.46 (XTA(RF)), Y1.2
unnamed: C20.2, U13.45 (VR_DIG(RF))
unnamed: C21.2, U13.44 (VR_ANA(RF))
unnamed: C23.1, C29.1, L1.2
unnamed: C23.2, L2.1
unnamed: C24.1, C26.1, L3.2
unnamed: C24.2, C27.1, L4.1
unnamed: C25.1, L2.2, L3.1
unnamed: D1.1 (K), R12.1
unnamed: D2.1 (RA), R11.2
unnamed: D2.3 (BA), R9.2
unnamed: D2.4 (GA), R10.2
unnamed: D3.1 (K), U14.23 (TXLED)
unnamed: D3.2 (A), R13.2
unnamed: D4.1 (K), U14.22 (RXLED)
unnamed: D4.2 (A), R14.2
unnamed: D5.1 (K), R16.1
unnamed: D6.2 (A), R15.2
unnamed: L1.1, U13.39 (RFIO(RF))
unnamed: P4.2 (D-), U14.16 (USBD-)
unnamed: P4.3 (D+), U14.15 (USBD+)
unnamed: Q1.2 (B), R4.1
unnamed: Q1.3 (C), R1.2, SP1.2
unnamed: R2.2, U1.4 (DIN)
unnamed: R5.1, U16.5 (PROG)
unnamed: R7.2, U13.48 (RESET(RF))
unnamed: R15.1, R16.2, U16.1 (STAT)
unnamed: TP1.1, U13.12 (PTA4)
unnamed: U1.2 (DOUT), U2.4 (DIN)
unnamed: U2.2 (DOUT), U3.4 (DIN)
unnamed: U3.2 (DOUT), U4.4 (DIN)
unnamed: U4.2 (DOUT), U5.4 (DIN)
unnamed: U5.2 (DOUT), U6.4 (DIN)
unnamed: U6.2 (DOUT), U7.4 (DIN)
unnamed: U7.2 (DOUT), U8.4 (DIN)
unnamed: U8.2 (DOUT), U9.4 (DIN)
unnamed: U10.2 (DOUT), U11.4 (DIN)
unnamed: U9.2 (DOUT), U10.4 (DIN)
unnamed: U11.2 (DOUT), U12.4 (DIN)
unnamed: U12.2 (DOUT), W4.1
unnamed: U13.23 (PTC4), W14.1
unnamed: U13.24 (PTC1), W12.1
unnamed: U13.26 (PTC3), W13.1
unnamed: U13.41 (PA_BOOST(RF)), W5.1
PTB0: P2.35, R9.1, U13.17 (PTB0)
PTB1: R10.1, U13.18 (PTB1), W11.1
PTE16: R11.1, U13.5 (PTE16/ADC0_DP1/ADCO_SE1/SPI0_PCS0/TPM/U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)
PWM_SOUND: R4.2, U13.25 (PTC2)
RESET_TGTMCU: J2.10 (~RESET), SW1.2, U13.33 (PTA20/RESETB)
RF_RESET: R7.1, U13.9 (PTE30)
TILTSENS: P1.1, R6.1, U13.29 (PTD6), W8.1
TOUCH_CS: P2.30, U13.8 (PTE19)
UART0_CTS: U13.22 (PTB17), U14.3 (~RTS)
UART0_RTS: U13.21 (PTB2), U14.11 (~CTS)
UART_RX: TP2.1, U13.14 (PTA1), U14.1 (TXD)
UART_TX: TP3.1, U13.13 (PTA2/UART0_TX), U14.5 (RXD)
VBAT: BT1.1, C13.1, C15.1, TP4.1, U1.1 (VDD), U2.1 (VDD), U3.1 (VDD), U4.1 (VDD), U15.1 (VIN), U15.3 (EN), U16.3 (VBAT)
VCC: C1.1, C2.1, C3.1, C4.1, C5.1, C6.1, C7.1, C8.1, C9.1, C10.1, C11.1, C12.1, C22.1, D1.2 (A), D2.2 (K), J2.1 (VTref), P1.2, P2.2, R1.1, R8.1, SP1.1, U5.1 (VDD), U6.1 (VDD), U7.1 (VDD), U8.1 (VDD), U9.1 (VDD), U10.1 (VDD), U11.1 (VDD), U12.1 (VDD), U13.1 (VREFH), U13.19 (VDD1), U13.35 (VBAT2(RF)), U13.55 (VDD2), U13.56 (VDDAD), U15.5 (VOUT)
VUSB: C14.1, C30.1, C31.1, D5.2 (A), P4.1 (VBUS), R3.2, R13.1, R14.1, U14.20 (VCC), U16.4 (VDD); also elsewhere on the board

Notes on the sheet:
Level Shift + Decoupling
Circular LED Ring / 12 RGB LEDs
JTAG/SWD
Display
Audio
Power / Charge
RFIO_EXT
RF FILTER - Shield This?
SPI BUS
Orientation
CONSOLE (USB TO SERIAL)
DEBUG LED
Matches original pins on KW01 dev board
LDO 76333 is pre-programmed for 3.3V OUT, 150mA no FB resistors
CHARGE RATE 10k=100mA 5.0K=200mA 2.0K=500mA 1.0K=1000mA
3.3V
VBAT = 3.7V Direct from Battery
these values not tested
